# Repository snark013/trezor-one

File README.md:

# trezor-one

Trezor One cryptocurrency wallet.

Modified version of the original one from https://github.com/trezor/trezor-hardware

Modifications include -
- all R and C components of size 0603
- other buttons
- USB type-C connector

As a result, the board is a bit longer and the case had to be modified as well.
The circuitry and firmware are original (only added two resistors to the circuit to allow the USB host to detect the connected device by the type-C connector).

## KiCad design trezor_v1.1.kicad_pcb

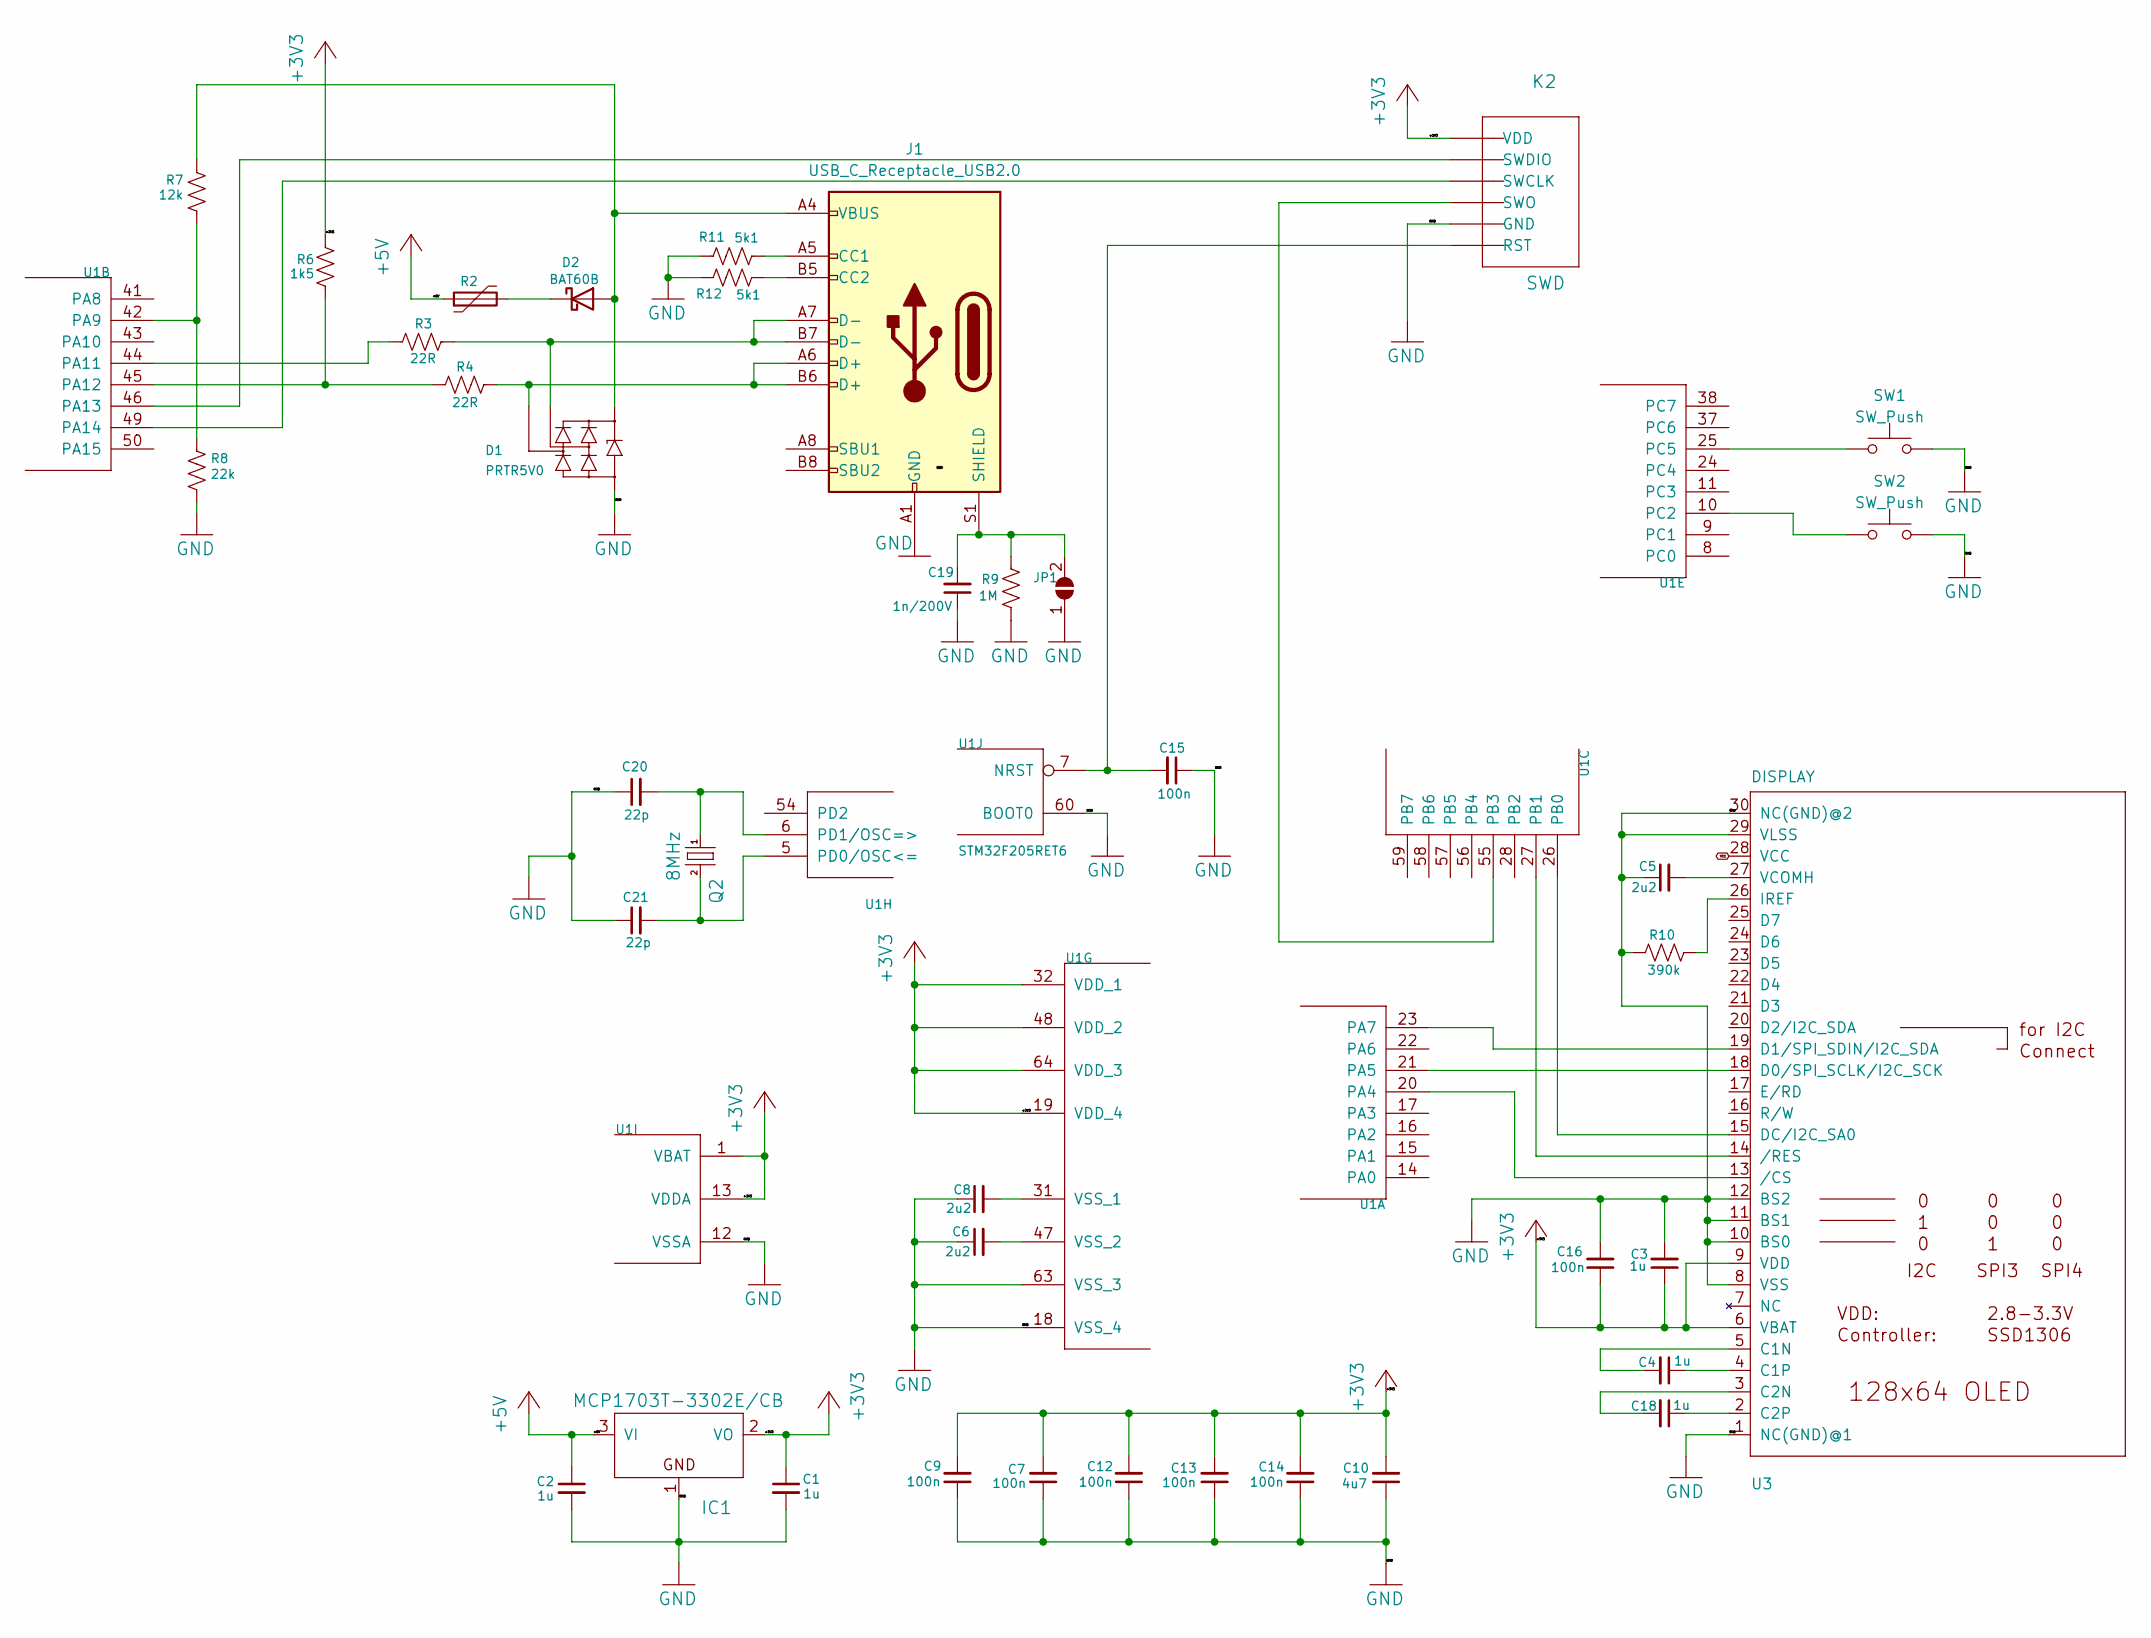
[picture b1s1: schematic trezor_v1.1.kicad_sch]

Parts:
C1, C2, C3, C4, C18: 1u; C_0603_1608Metric
C5, C6, C8: 2u2; C_0603_1608Metric
C7, C9, C12, C13, C14, C15, C16: 100n; C_0603_1608Metric
C10: 4u7; C_0603_1608Metric
C19: 1n/200V; C_0603_1608Metric
C20, C21: 22p; C_0603_1608Metric
D1: PRTR5V0; SOT-143_Handsoldering
D2: BAT60B; D_SOD-323_HandSoldering
IC1: MCP1703T-3302E/CB; TSOT-23
J1: USB_C_Receptacle_USB2.0; USB_C_Receptacle_HRO_TYPE-C-31-M-12
JP1: SolderJumper_2_Open; SolderJumper-2_P1.3mm_Open_RoundedPad1.0x1.5mm
K2: SWD
Q2: 8MHz; Crystal_SMD_3225-4Pin_3.2x2.5mm
R2: MF-FSMF020X-2; Fuse_0603_1608Metric_Pad1.05x0.95mm_HandSolder
R3, R4: 22R; R_0603_1608Metric
R6: 1k5; R_0603_1608Metric
R7: 12k; R_0603_1608Metric
R8: 22k; R_0603_1608Metric
R9: 1M; R_0603_1608Metric
R10: 390k; R_0603_1608Metric
R11, R12: 5k1; R_0603_1608Metric
SW1, SW2: SW_Push; SW_SPST_EVQP2
U1: STM32F205RET6; TQFP-64_10x10mm_P0.5mm
U3: DISPLAY; UG-2864HSWEG01_0.96IN_WRAPAROUND

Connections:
+3V3: C1.1, C3.1, C7.2, C9.2, C10.2, C12.2, C13.2, C14.2, C16.1, IC1.2 (VO), K2.6 (VDD), R6.1, U1.1 (VBAT), U1.13 (VDDA), U1.19 (VDD_4), U1.32 (VDD_1), U1.48 (VDD_2), U1.64 (VDD_3), U3.6 (VBAT), U3.9 (VDD)
+5V: C2.1, IC1.3 (VI), R2.1
GND: C1.2, C2.2, C3.2, C5.1, C6.1, C7.1, C8.1, C9.1, C10.1, C12.1, C13.1, C14.1, C15.1, C16.2, C19.1, C20.1, C21.1, D1.1 (GND), IC1.1 (GND), J1.A1 (GND), J1.A12 (GND), J1.B1 (GND), J1.B12 (GND), JP1.1 (A), K2.2 (GND), R8.1, R9.1, R10.1, R11.1, R12.1, SW1.2, SW2.2, U1.12 (VSSA), U1.18 (VSS_4), U1.60 (BOOT0), U1.63 (VSS_3), U3.1 (NC(GND)@1), U3.8 (VSS), U3.10 (BS0), U3.11 (BS1), U3.12 (BS2), U3.29 (VLSS), U3.30 (NC(GND)@2)
unnamed: D1.2 (I/O1), J1.A7 (D-), J1.B7 (D-), R3.2
unnamed: D1.3 (I/O2), J1.A6 (D+), J1.B6 (D+), R4.2
unnamed: D1.4 (VCC), D2.2 (A), J1.A4 (VBUS), J1.A9 (VBUS), J1.B4 (VBUS), J1.B9 (VBUS), R7.2
unnamed: D2.1 (K), R2.2
unnamed: J1.A5 (CC1), R12.2
unnamed: J1.B5 (CC2), R11.2
unnamed: C19.2, J1.S1 (SHIELD), JP1.2 (B), R9.2
unnamed: C15.2, K2.1 (RST), U1.7 (NRST)
unnamed: K2.4 (SWCLK), U1.49 (PA14)
unnamed: K2.5 (SWDIO), U1.46 (PA13)
unnamed: K2.3 (SWO), U1.55 (PB3)
unnamed: C21.2, Q2.3 (2), U1.5 (PD0/OSC<=)
unnamed: U1.20 (PA4), U3.13 (/CS)
unnamed: U1.21 (PA5), U3.18 (D0/SPI_SCLK/I2C_SCK)
unnamed: U1.23 (PA7), U3.19 (D1/SPI_SDIN/I2C_SDA)
unnamed: R7.1, R8.2, U1.42 (PA9)
unnamed: R3.1, U1.44 (PA11)
unnamed: R4.1, R6.2, U1.45 (PA12)
unnamed: U1.26 (PB0), U3.15 (DC/I2C_SA0)
unnamed: U1.27 (PB1), U3.14 (/RES)
unnamed: SW2.1, U1.10 (PC2)
unnamed: SW1.1, U1.25 (PC5)
unnamed: C8.2, U1.31 (VSS_1)
unnamed: C6.2, U1.47 (VSS_2)
unnamed: C20.2, Q2.1, U1.6 (PD1/OSC=>)
unnamed: C4.2, U3.5 (C1N)
unnamed: C4.1, U3.4 (C1P)
unnamed: C18.2, U3.3 (C2N)
unnamed: C18.1, U3.2 (C2P)
unnamed: R10.2, U3.26 (IREF)
unnamed: C5.2, U3.27 (VCOMH)
VCC: U3.28 (VCC)

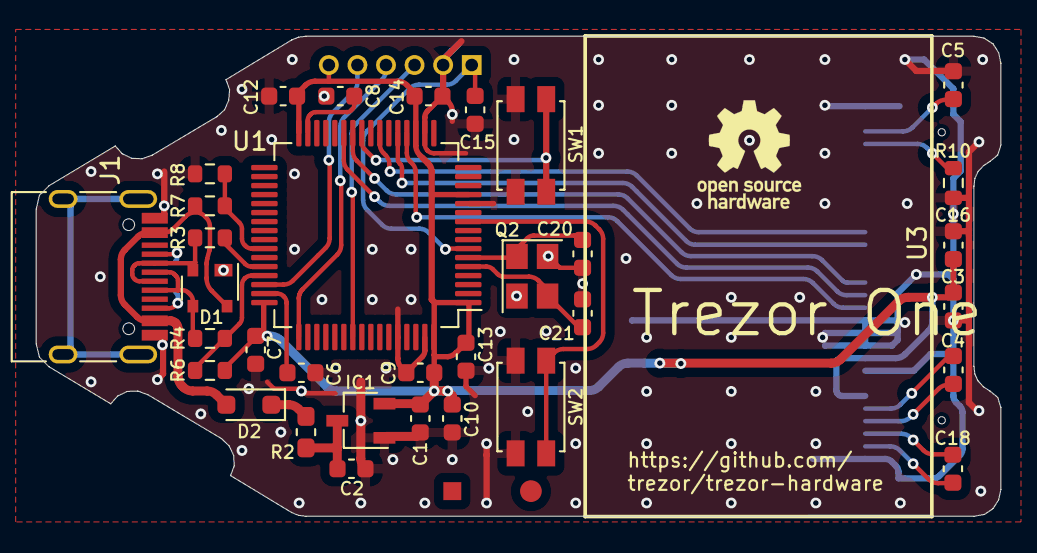
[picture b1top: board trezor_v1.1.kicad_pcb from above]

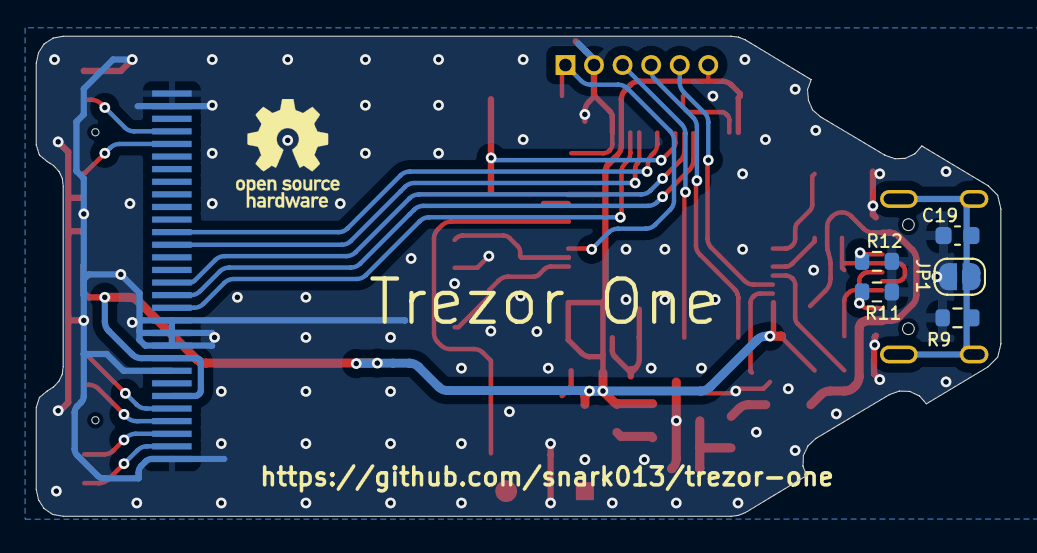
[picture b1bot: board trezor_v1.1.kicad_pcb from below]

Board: 2 copper layers, 53.6 x 26.7 mm, 42 parts (5 on the bottom side), 34 nets.

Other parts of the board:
U$3: BADMARK
U$4: CENTR

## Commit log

2023-11-21 ChangeLog: - initial version.
2023-11-21 ChangeLog: - add images.
